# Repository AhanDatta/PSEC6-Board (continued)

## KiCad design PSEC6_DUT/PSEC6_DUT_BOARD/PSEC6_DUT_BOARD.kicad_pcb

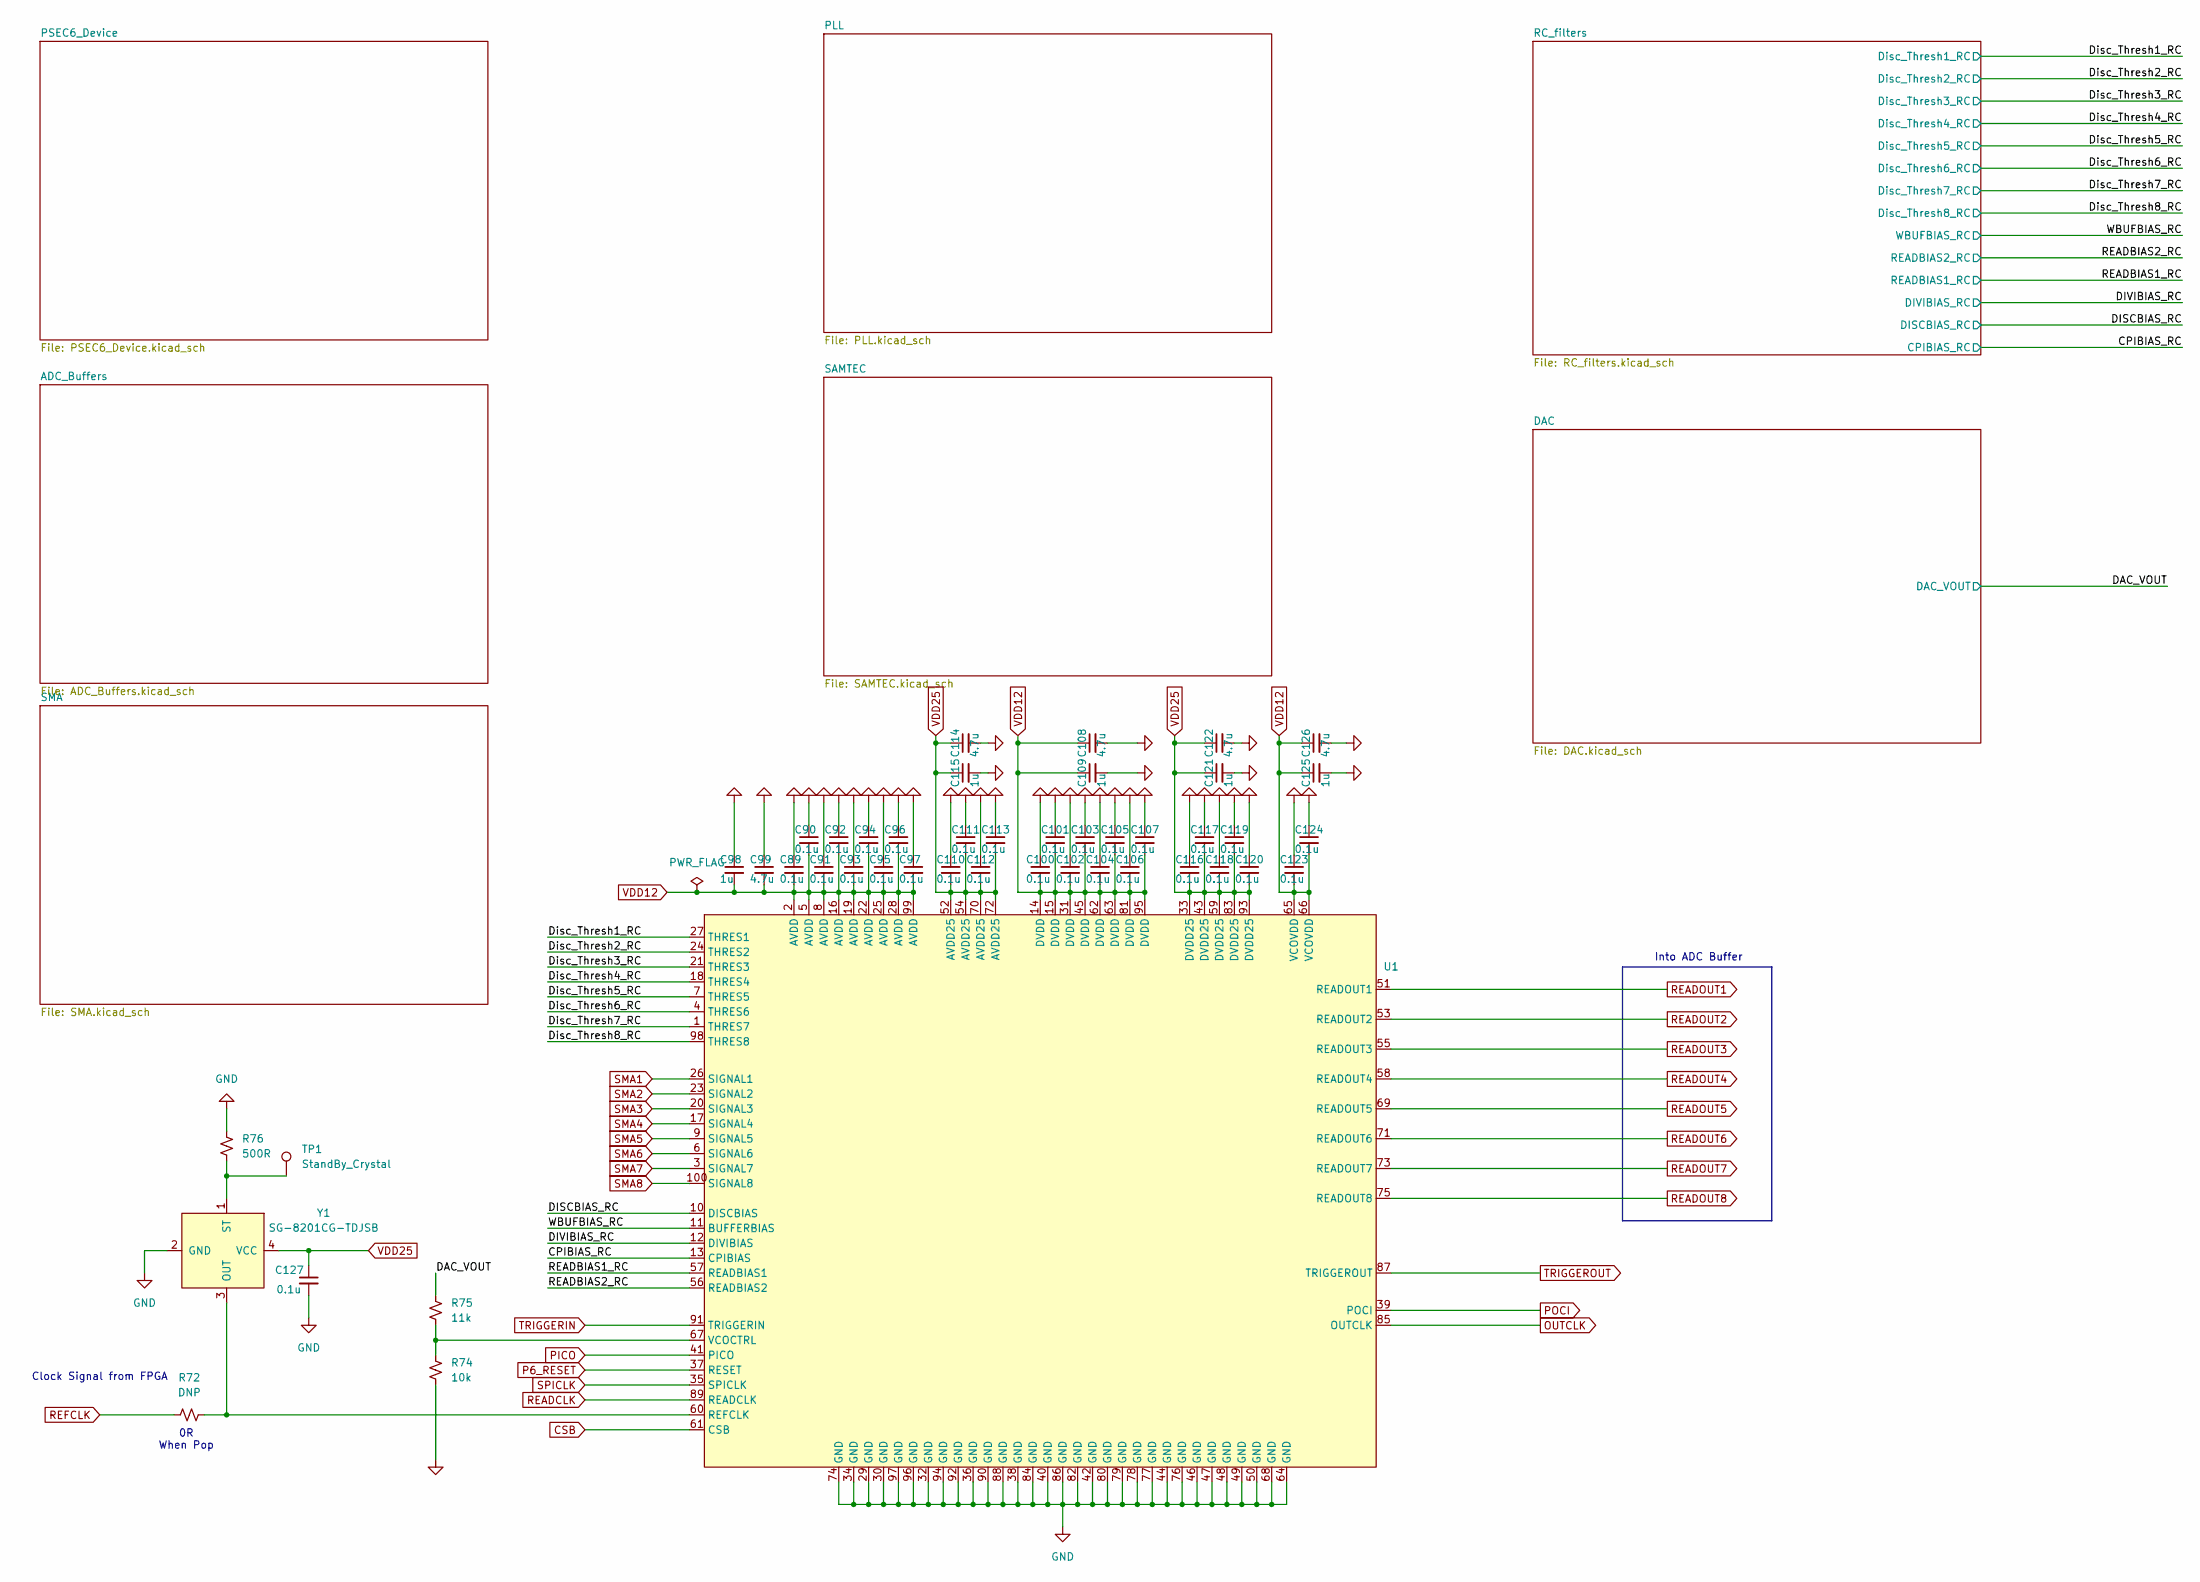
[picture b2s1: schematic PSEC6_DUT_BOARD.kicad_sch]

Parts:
C89, C90, C91, C92, C93, C94, C95, C96, C97, C100, C101, C102, C103, C104, C105, C106, C107, C110, C111, C112, C113, C116, C117, C118, C119, C120, C123, C124, C127: 0.1u; C_0603_1608Metric
C98, C109, C115, C121, C125: 1u; C_0603_1608Metric
C99, C108, C114, C122, C126: 4.7u; C_0603_1608Metric
R72: DNP; R_0603_1608Metric
R74: 10k; R_0603_1608Metric
R75: 11k; R_0603_1608Metric
R76: 500R; R_0603_1608Metric
TP1: StandBy_Crystal; TestPoint_THTPad_1.5x1.5mm_Drill0.7mm
U1: ArtInChip_QFN-100-1EP_12x12mm_P0.4mm_EP7.4x7.4mm
Y1: SG-8201CG-TDJSB

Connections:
/CPIBIAS_RC: U1.13 (CPIBIAS); also elsewhere on the board
/DAC_VOUT: R75.2; also elsewhere on the board
/DISCBIAS_RC: U1.10 (DISCBIAS); also elsewhere on the board
/DIVIBIAS_RC: U1.12 (DIVIBIAS); also elsewhere on the board
/Disc_Thresh1_RC: U1.27 (THRES1); also elsewhere on the board
/Disc_Thresh2_RC: U1.24 (THRES2); also elsewhere on the board
/Disc_Thresh3_RC: U1.21 (THRES3); also elsewhere on the board
/Disc_Thresh4_RC: U1.18 (THRES4); also elsewhere on the board
/Disc_Thresh5_RC: U1.7 (THRES5); also elsewhere on the board
/Disc_Thresh6_RC: U1.4 (THRES6); also elsewhere on the board
/Disc_Thresh7_RC: U1.1 (THRES7); also elsewhere on the board
/Disc_Thresh8_RC: U1.98 (THRES8); also elsewhere on the board
/READBIAS1_RC: U1.57 (READBIAS1); also elsewhere on the board
/READBIAS2_RC: U1.56 (READBIAS2); also elsewhere on the board
/WBUFBIAS_RC: U1.11 (BUFFERBIAS); also elsewhere on the board
CSB: U1.61 (CSB); also elsewhere on the board
GND: C89.1, C90.1, C91.1, C92.1, C93.1, C94.1, C95.1, C96.1, C97.1, C98.1, C99.1, C100.1, C101.1, C102.1, C103.1, C104.1, C105.1, C106.1, C107.1, C108.2, C109.2, C110.1, C111.1, C112.1, C113.1, C114.2, C115.2, C116.1, C117.1, C118.1, C119.1, C120.1, C121.2, C122.2, C123.1, C124.1, C125.2, C126.2, C127.2, R74.1, R76.2, U1.29 (GND), U1.30 (GND), U1.32 (GND), U1.34 (GND), U1.36 (GND), U1.38 (GND), U1.40 (GND), U1.42 (GND), U1.44 (GND), U1.46 (GND), U1.47 (GND), U1.48 (GND), U1.49 (GND), U1.50 (GND), U1.64 (GND), U1.68 (GND), U1.74 (GND), U1.76 (GND), U1.77 (GND), U1.78 (GND), U1.79 (GND), U1.80 (GND), U1.82 (GND), U1.84 (GND), U1.86 (GND), U1.88 (GND), U1.90 (GND), U1.92 (GND), U1.94 (GND), U1.96 (GND), U1.97 (GND), Y1.2 (GND); also elsewhere on the board
unnamed: R72.2, U1.60 (REFCLK), Y1.3 (OUT)
unnamed: R74.2, R75.1, U1.67 (VCOCTRL)
unnamed: R76.1, TP1.1 (1_1), Y1.1 (ST)
OUTCLK: U1.85 (OUTCLK); also elsewhere on the board
P6_RESET: U1.37 (RESET); also elsewhere on the board
PICO: U1.41 (PICO); also elsewhere on the board
POCI: U1.39 (POCI); also elsewhere on the board
READCLK: U1.89 (READCLK); also elsewhere on the board
READOUT1: U1.51 (READOUT1); also elsewhere on the board
READOUT2: U1.53 (READOUT2); also elsewhere on the board
READOUT3: U1.55 (READOUT3); also elsewhere on the board
READOUT4: U1.58 (READOUT4); also elsewhere on the board
READOUT5: U1.69 (READOUT5); also elsewhere on the board
READOUT6: U1.71 (READOUT6); also elsewhere on the board
READOUT7: U1.73 (READOUT7); also elsewhere on the board
READOUT8: U1.75 (READOUT8); also elsewhere on the board
REFCLK: R72.1; also elsewhere on the board
SMA1: U1.26 (SIGNAL1); also elsewhere on the board
SMA2: U1.23 (SIGNAL2); also elsewhere on the board
SMA3: U1.20 (SIGNAL3); also elsewhere on the board
SMA4: U1.17 (SIGNAL4); also elsewhere on the board
SMA5: U1.9 (SIGNAL5); also elsewhere on the board
SMA6: U1.6 (SIGNAL6); also elsewhere on the board
SMA7: U1.3 (SIGNAL7); also elsewhere on the board
SMA8: U1.100 (SIGNAL8); also elsewhere on the board
SPICLK: U1.35 (SPICLK); also elsewhere on the board
TRIGGERIN: U1.91 (TRIGGERIN); also elsewhere on the board
TRIGGEROUT: U1.87 (TRIGGEROUT); also elsewhere on the board
VDD12: C89.2, C90.2, C91.2, C92.2, C93.2, C94.2, C95.2, C96.2, C97.2, C98.2, C99.2, C100.2, C101.2, C102.2, C103.2, C104.2, C105.2, C106.2, C107.2, C108.1, C109.1, C123.2, C124.2, C125.1, C126.1, U1.2 (AVDD), U1.5 (AVDD), U1.8 (AVDD), U1.14 (DVDD), U1.15 (DVDD), U1.16 (AVDD), U1.19 (AVDD), U1.22 (AVDD), U1.25 (AVDD), U1.28 (AVDD), U1.31 (DVDD), U1.45 (DVDD), U1.62 (DVDD), U1.63 (DVDD), U1.65 (VCOVDD), U1.66 (VCOVDD), U1.81 (DVDD), U1.95 (DVDD), U1.99 (AVDD); also elsewhere on the board
VDD25: C110.2, C111.2, C112.2, C113.2, C114.1, C115.1, C116.2, C117.2, C118.2, C119.2, C120.2, C121.1, C122.1, C127.1, U1.33 (DVDD25), U1.43 (DVDD25), U1.52 (AVDD25), U1.54 (AVDD25), U1.59 (DVDD25), U1.70 (AVDD25), U1.72 (AVDD25), U1.83 (DVDD25), U1.93 (DVDD25), Y1.4 (VCC); also elsewhere on the board

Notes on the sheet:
0R When Pop
Into ADC Buffer
Clock Signal from FPGA

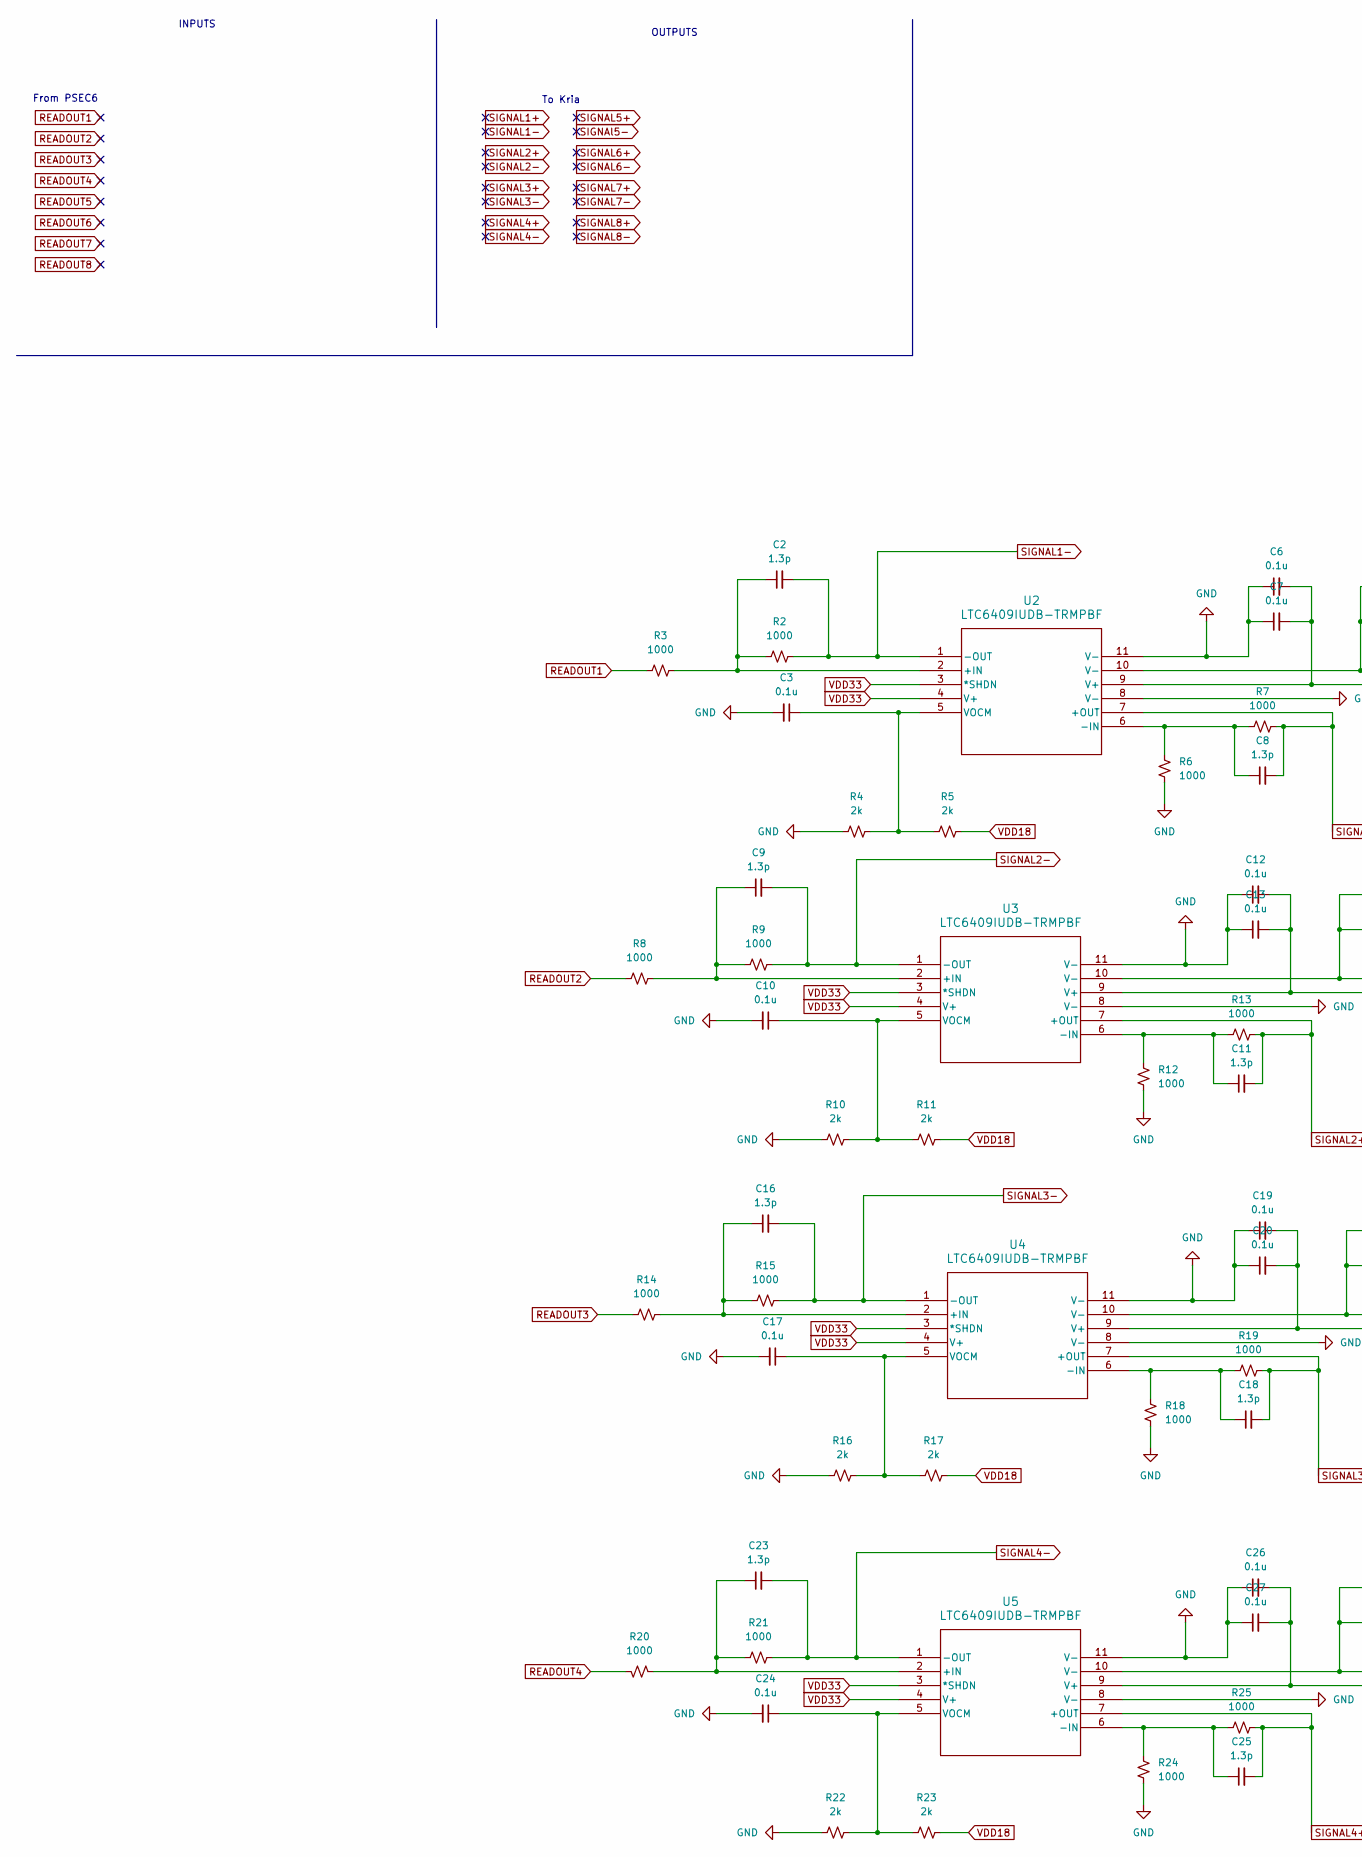
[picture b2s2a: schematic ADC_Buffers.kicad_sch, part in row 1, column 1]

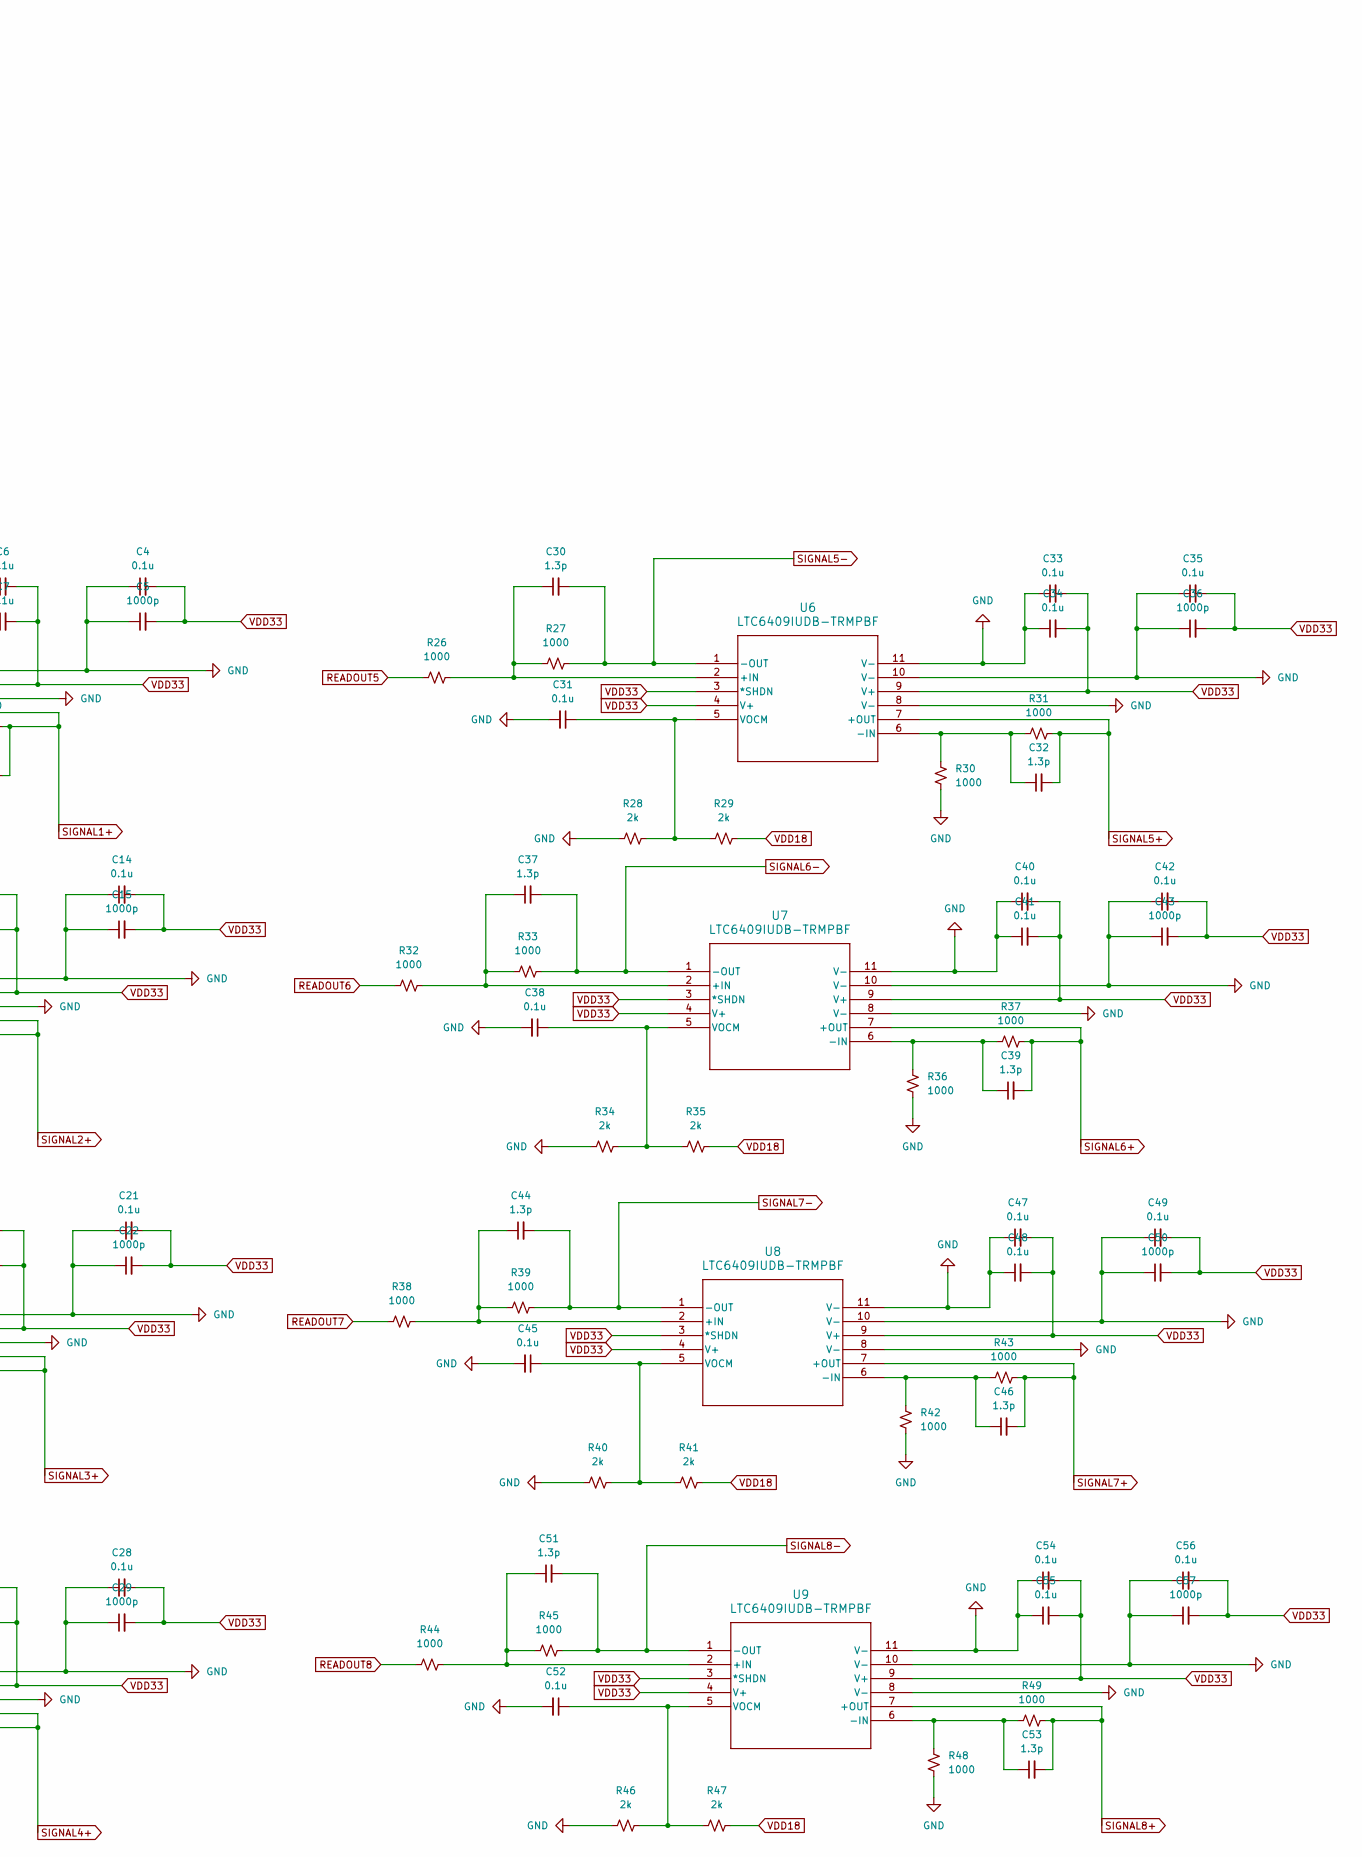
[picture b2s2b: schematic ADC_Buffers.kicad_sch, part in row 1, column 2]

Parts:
C2, C8, C9, C11, C16, C18, C23, C25, C30, C32, C37, C39, C44, C46, C51, C53: 1.3p; C_0603_1608Metric
C3, C4, C6, C7, C10, C12, C13, C14, C17, C19, C20, C21, C24, C26, C27, C28, C31, C33, C34, C35, C38, C40, C41, C42, C45, C47, C48, C49, C52, C54, C55, C56: 0.1u; C_0603_1608Metric
C5, C15, C22, C29, C36, C43, C50, C57: 1000p; C_0603_1608Metric
R2, R3, R6, R7, R8, R9, R12, R13, R14, R15, R18, R19, R20, R21, R24, R25, R26, R27, R30, R31, R32, R33, R36, R37, R38, R39, R42, R43, R44, R45, R48, R49: 1000; R_0603_1608Metric
R4, R5, R10, R11, R16, R17, R22, R23, R28, R29, R34, R35, R40, R41, R46, R47: 2k; R_0603_1608Metric
U2, U3, U4, U5, U6, U7, U8, U9: LTC6409IUDB-TRMPBF; QFN-10_UDB_LIT

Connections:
GND: C3.2, C4.1, C5.1, C6.1, C7.1, C10.2, C12.1, C13.1, C14.1, C15.1, C17.2, C19.1, C20.1, C21.1, C22.1, C24.2, C26.1, C27.1, C28.1, C29.1, C31.2, C33.1, C34.1, C35.1, C36.1, C38.2, C40.1, C41.1, C42.1, C43.1, C45.2, C47.1, C48.1, C49.1, C50.1, C52.2, C54.1, C55.1, C56.1, C57.1, R4.1, R6.1, R10.1, R12.1, R16.1, R18.1, R22.1, R24.1, R28.1, R30.1, R34.1, R36.1, R40.1, R42.1, R46.1, R48.1, U2.8 (V-), U2.10 (V-), U2.11 (V-), U3.8 (V-), U3.10 (V-), U3.11 (V-), U4.8 (V-), U4.10 (V-), U4.11 (V-), U5.8 (V-), U5.10 (V-), U5.11 (V-), U6.8 (V-), U6.10 (V-), U6.11 (V-), U7.8 (V-), U7.10 (V-), U7.11 (V-), U8.8 (V-), U8.10 (V-), U8.11 (V-), U9.8 (V-), U9.10 (V-), U9.11 (V-); also elsewhere on the board
unnamed: C2.1, R2.1, R3.2, U2.2 (+IN)
unnamed: C8.1, R6.2, R7.2, U2.6 (-IN)
unnamed: C3.1, R4.2, R5.1, U2.5 (VOCM)
unnamed: C9.1, R8.2, R9.1, U3.2 (+IN)
unnamed: C11.1, R12.2, R13.2, U3.6 (-IN)
unnamed: C10.1, R10.2, R11.1, U3.5 (VOCM)
unnamed: C16.1, R14.2, R15.1, U4.2 (+IN)
unnamed: C18.1, R18.2, R19.2, U4.6 (-IN)
unnamed: C17.1, R16.2, R17.1, U4.5 (VOCM)
unnamed: C23.1, R20.1, R21.1, U5.2 (+IN)
unnamed: C25.1, R24.2, R25.2, U5.6 (-IN)
unnamed: C24.1, R22.2, R23.1, U5.5 (VOCM)
unnamed: C30.1, R26.2, R27.1, U6.2 (+IN)
unnamed: C32.1, R30.2, R31.2, U6.6 (-IN)
unnamed: C31.1, R28.2, R29.1, U6.5 (VOCM)
unnamed: C37.1, R32.2, R33.1, U7.2 (+IN)
unnamed: C39.1, R36.2, R37.2, U7.6 (-IN)
unnamed: C38.1, R34.2, R35.1, U7.5 (VOCM)
unnamed: C44.1, R38.2, R39.1, U8.2 (+IN)
unnamed: C46.1, R42.2, R43.2, U8.6 (-IN)
unnamed: C45.1, R40.2, R41.1, U8.5 (VOCM)
unnamed: C51.1, R44.2, R45.1, U9.2 (+IN)
unnamed: C53.1, R48.2, R49.2, U9.6 (-IN)
unnamed: C52.1, R46.2, R47.1, U9.5 (VOCM)
READOUT1: R3.1; also elsewhere on the board
READOUT2: R8.1; also elsewhere on the board
READOUT3: R14.1; also elsewhere on the board
READOUT4: R20.2; also elsewhere on the board
READOUT5: R26.1; also elsewhere on the board
READOUT6: R32.1; also elsewhere on the board
READOUT7: R38.1; also elsewhere on the board
READOUT8: R44.1; also elsewhere on the board
SIGNAL1+: C8.2, R7.1, U2.7 (+OUT); also elsewhere on the board
SIGNAL1-: C2.2, R2.2, U2.1 (-OUT); also elsewhere on the board
SIGNAL2+: C11.2, R13.1, U3.7 (+OUT); also elsewhere on the board
SIGNAL2-: C9.2, R9.2, U3.1 (-OUT); also elsewhere on the board
SIGNAL3+: C18.2, R19.1, U4.7 (+OUT); also elsewhere on the board
SIGNAL3-: C16.2, R15.2, U4.1 (-OUT); also elsewhere on the board
SIGNAL4+: C25.2, R25.1, U5.7 (+OUT); also elsewhere on the board
SIGNAL4-: C23.2, R21.2, U5.1 (-OUT); also elsewhere on the board
SIGNAL5+: C32.2, R31.1, U6.7 (+OUT); also elsewhere on the board
SIGNAL5-: C30.2, R27.2, U6.1 (-OUT); also elsewhere on the board
SIGNAL6+: C39.2, R37.1, U7.7 (+OUT); also elsewhere on the board
SIGNAL6-: C37.2, R33.2, U7.1 (-OUT); also elsewhere on the board
SIGNAL7+: C46.2, R43.1, U8.7 (+OUT); also elsewhere on the board
SIGNAL7-: C44.2, R39.2, U8.1 (-OUT); also elsewhere on the board
SIGNAL8+: C53.2, R49.1, U9.7 (+OUT); also elsewhere on the board
SIGNAL8-: C51.2, R45.2, U9.1 (-OUT); also elsewhere on the board
VDD18: R5.2, R11.2, R17.2, R23.2, R29.2, R35.2, R41.2, R47.2; also elsewhere on the board
VDD33: C4.2, C5.2, C6.2, C7.2, C12.2, C13.2, C14.2, C15.2, C19.2, C20.2, C21.2, C22.2, C26.2, C27.2, C28.2, C29.2, C33.2, C34.2, C35.2, C36.2, C40.2, C41.2, C42.2, C43.2, C47.2, C48.2, C49.2, C50.2, C54.2, C55.2, C56.2, C57.2, U2.3 (*SHDN), U2.4 (V+), U2.9 (V+), U3.3 (*SHDN), U3.4 (V+), U3.9 (V+), U4.3 (*SHDN), U4.4 (V+), U4.9 (V+), U5.3 (*SHDN), U5.4 (V+), U5.9 (V+), U6.3 (*SHDN), U6.4 (V+), U6.9 (V+), U7.3 (*SHDN), U7.4 (V+), U7.9 (V+), U8.3 (*SHDN), U8.4 (V+), U8.9 (V+), U9.3 (*SHDN), U9.4 (V+), U9.9 (V+); also elsewhere on the board

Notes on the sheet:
OUTPUTS
From PSEC6
INPUTS
To Kria

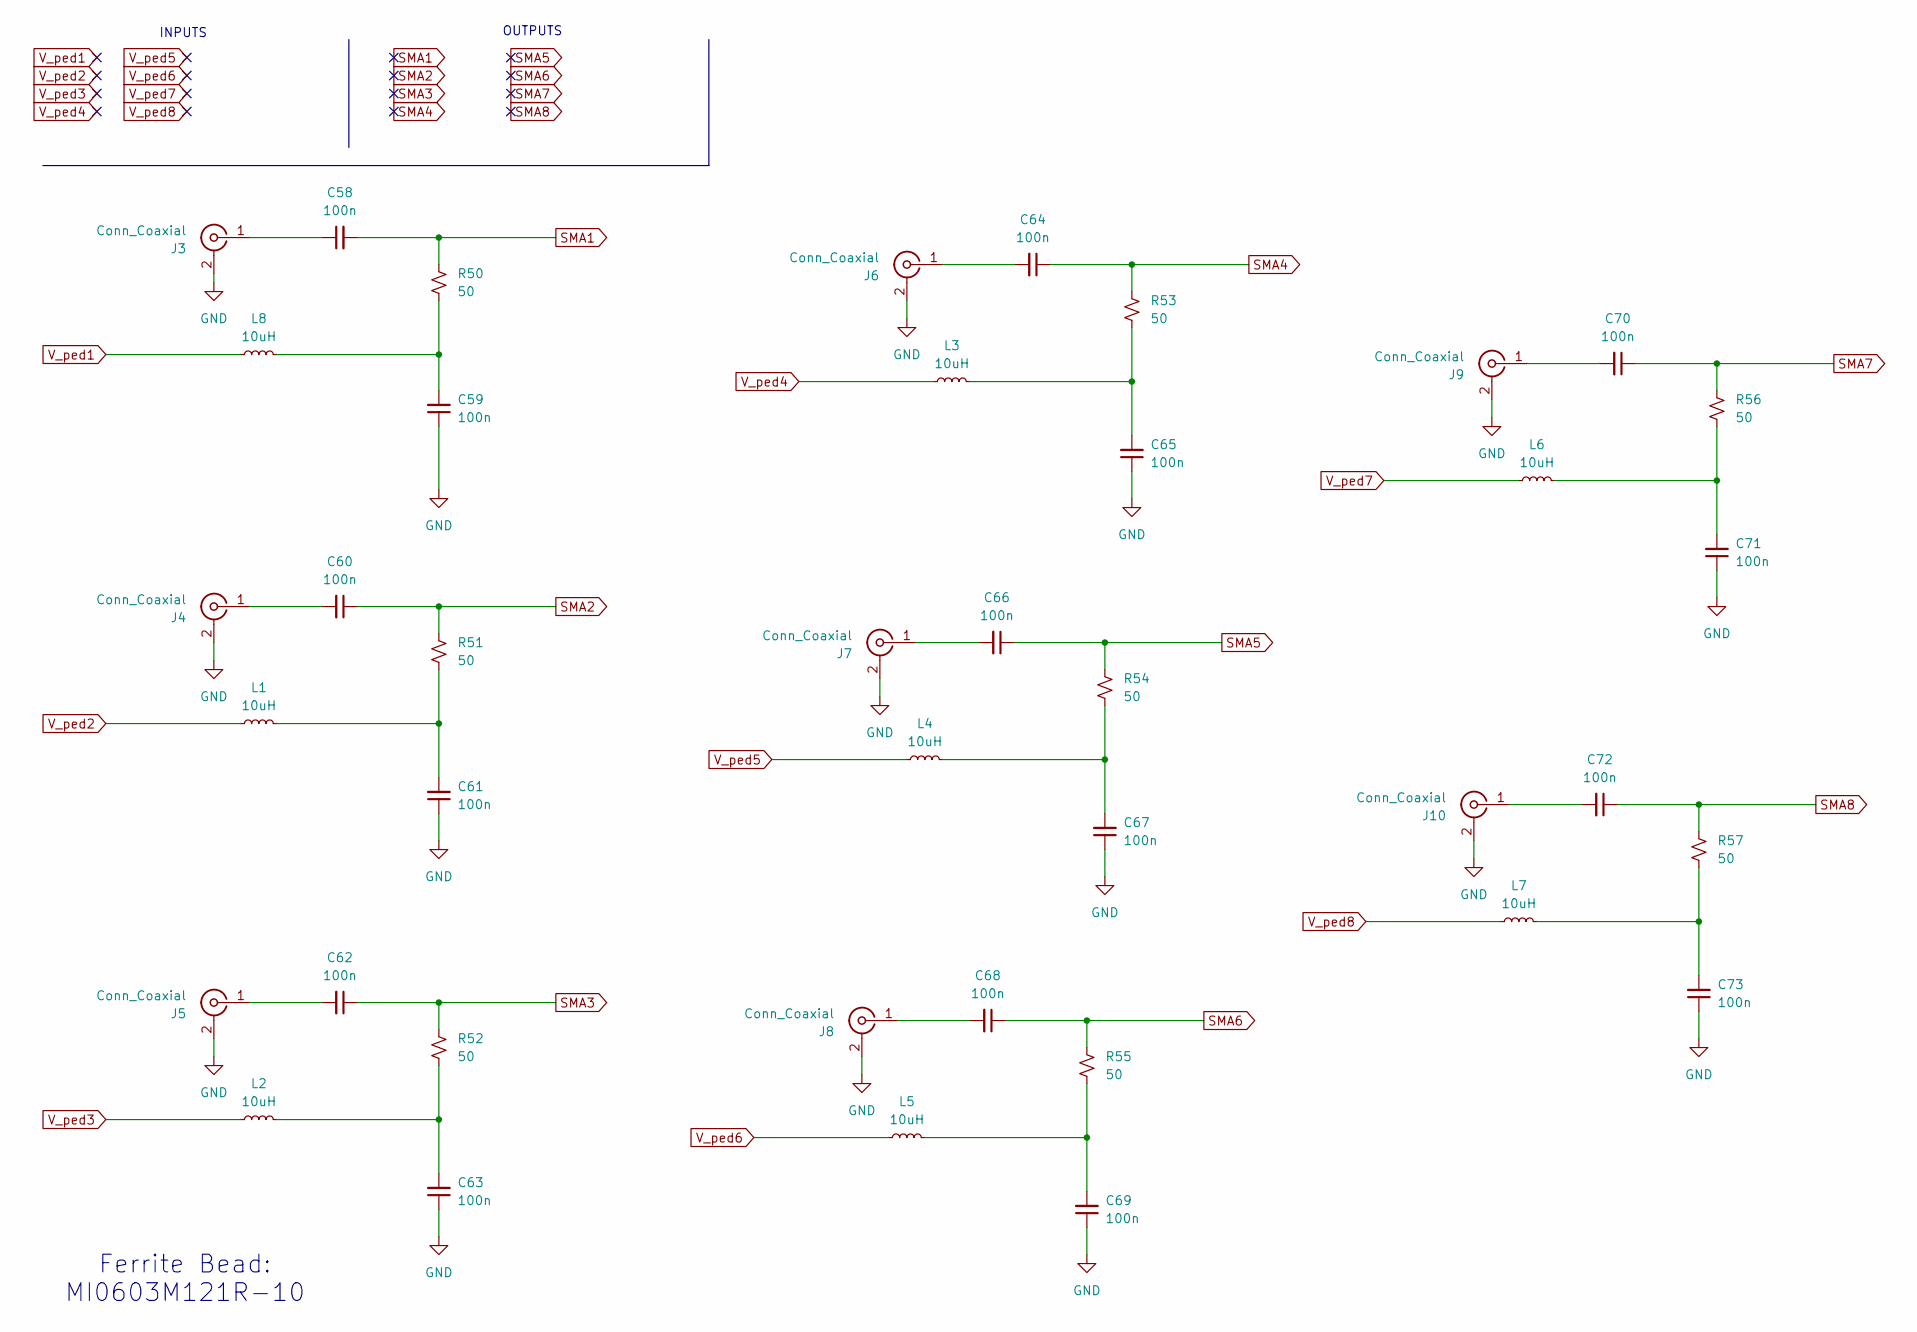
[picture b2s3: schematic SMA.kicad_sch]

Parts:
C58, C59, C60, C61, C62, C63, C64, C65, C66, C67, C68, C69, C70, C71, C72, C73: 100n; C_0603_1608Metric
J3, J4, J5, J6, J7, J8, J9, J10: Conn_Coaxial; SMA_Amphenol_132134-14_Vertical
L1, L2, L3, L4, L5, L6, L7, L8: 10uH; IND_LQH2MCN100K02L
R50, R51, R52, R53, R54, R55, R56, R57: 50; R_0603_1608Metric

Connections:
GND: C59.1, C61.1, C63.1, C65.1, C67.1, C69.1, C71.1, C73.1, J3.2 (Ext), J4.2 (Ext), J5.2 (Ext), J6.2 (Ext), J7.2 (Ext), J8.2 (Ext), J9.2 (Ext), J10.2 (Ext); also elsewhere on the board
unnamed: C59.2, L8.2, R50.2
unnamed: C61.2, L1.2, R51.2
unnamed: C63.2, L2.2, R52.2
unnamed: C65.2, L3.2, R53.2
unnamed: C67.2, L4.2, R54.2
unnamed: C69.2, L5.2, R55.2
unnamed: C71.2, L6.2, R56.2
unnamed: C73.2, L7.2, R57.2
unnamed: C58.1, J3.1 (In)
unnamed: C60.2, J4.1 (In)
unnamed: C62.2, J5.1 (In)
unnamed: C64.2, J6.1 (In)
unnamed: C66.2, J7.1 (In)
unnamed: C68.2, J8.1 (In)
unnamed: C70.2, J9.1 (In)
unnamed: C72.2, J10.1 (In)
SMA1: C58.2, R50.1; also elsewhere on the board
SMA2: C60.1, R51.1; also elsewhere on the board
SMA3: C62.1, R52.1; also elsewhere on the board
SMA4: C64.1, R53.1; also elsewhere on the board
SMA5: C66.1, R54.1; also elsewhere on the board
SMA6: C68.1, R55.1; also elsewhere on the board
SMA7: C70.1, R56.1; also elsewhere on the board
SMA8: C72.1, R57.1; also elsewhere on the board
V_ped1: L8.1; also elsewhere on the board
V_ped2: L1.1; also elsewhere on the board
V_ped3: L2.1; also elsewhere on the board
V_ped4: L3.1; also elsewhere on the board
V_ped5: L4.1; also elsewhere on the board
V_ped6: L5.1; also elsewhere on the board
V_ped7: L6.1; also elsewhere on the board
V_ped8: L7.1; also elsewhere on the board

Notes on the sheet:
OUTPUTS
Ferrite Bead: MI0603M121R-10
INPUTS

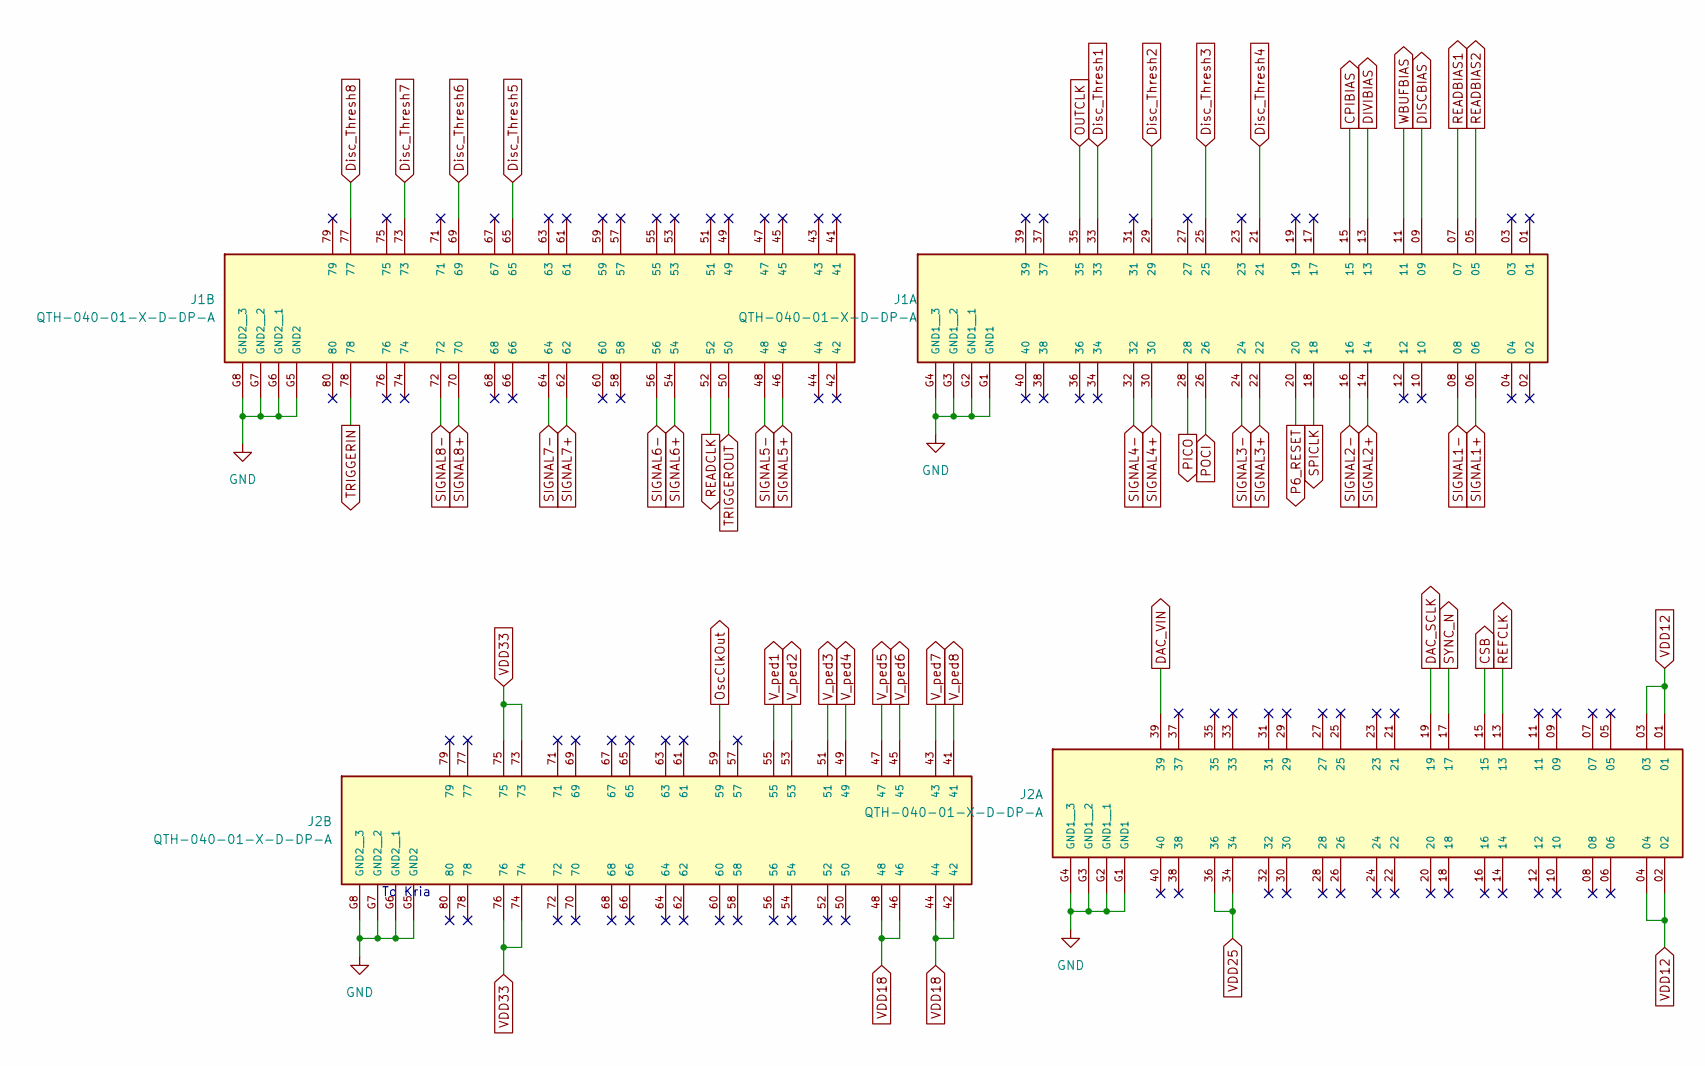
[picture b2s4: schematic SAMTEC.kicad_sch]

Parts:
J1, J2: QTH-040-01-X-D-DP-A; SAMTEC_QTH-040-01-X-D-DP-A; PARTREV L

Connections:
CPIBIAS: J1.15; also elsewhere on the board
CSB: J2.15; also elsewhere on the board
DAC_SCLK: J2.19; also elsewhere on the board
DAC_VIN: J2.39; also elsewhere on the board
DISCBIAS: J1.09; also elsewhere on the board
DIVIBIAS: J1.13; also elsewhere on the board
Disc_Thresh1: J1.33; also elsewhere on the board
Disc_Thresh2: J1.29; also elsewhere on the board
Disc_Thresh3: J1.25; also elsewhere on the board
Disc_Thresh4: J1.21; also elsewhere on the board
Disc_Thresh5: J1.77; also elsewhere on the board
Disc_Thresh6: J1.73; also elsewhere on the board
Disc_Thresh7: J1.69; also elsewhere on the board
Disc_Thresh8: J1.65; also elsewhere on the board
GND: J1.G1 (GND1), J1.G2 (GND1__1), J1.G3 (GND1__2), J1.G4 (GND1__3), J1.G5 (GND2), J1.G6 (GND2__1), J1.G7 (GND2__2), J1.G8 (GND2__3), J2.G1 (GND1), J2.G2 (GND1__1), J2.G3 (GND1__2), J2.G4 (GND1__3), J2.G5 (GND2), J2.G6 (GND2__1), J2.G7 (GND2__2), J2.G8 (GND2__3); also elsewhere on the board
OUTCLK: J1.35; also elsewhere on the board
OscClkOut: J2.59
P6_RESET: J1.20; also elsewhere on the board
PICO: J1.28; also elsewhere on the board
POCI: J1.26; also elsewhere on the board
READBIAS1: J1.07; also elsewhere on the board
READBIAS2: J1.05; also elsewhere on the board
READCLK: J1.52; also elsewhere on the board
REFCLK: J2.13; also elsewhere on the board
SIGNAL1+: J1.06; also elsewhere on the board
SIGNAL1-: J1.08; also elsewhere on the board
SIGNAL2+: J1.14; also elsewhere on the board
SIGNAL2-: J1.16; also elsewhere on the board
SIGNAL3+: J1.22; also elsewhere on the board
SIGNAL3-: J1.24; also elsewhere on the board
SIGNAL4+: J1.30; also elsewhere on the board
SIGNAL4-: J1.32; also elsewhere on the board
SIGNAL5+: J1.46; also elsewhere on the board
SIGNAL5-: J1.48; also elsewhere on the board
SIGNAL6+: J1.54; also elsewhere on the board
SIGNAL6-: J1.56; also elsewhere on the board
SIGNAL7+: J1.62; also elsewhere on the board
SIGNAL7-: J1.64; also elsewhere on the board
SIGNAL8+: J1.70; also elsewhere on the board
SIGNAL8-: J1.72; also elsewhere on the board
SPICLK: J1.18; also elsewhere on the board
SYNC_N: J2.17; also elsewhere on the board
TRIGGERIN: J1.78; also elsewhere on the board
TRIGGEROUT: J1.50; also elsewhere on the board
VDD12: J2.01, J2.02, J2.03, J2.04; also elsewhere on the board
VDD18: J2.42, J2.44, J2.46, J2.48; also elsewhere on the board
VDD25: J2.34, J2.36; also elsewhere on the board
VDD33: J2.73, J2.74, J2.75, J2.76; also elsewhere on the board
V_ped1: J2.55; also elsewhere on the board
V_ped2: J2.53; also elsewhere on the board
V_ped3: J2.51; also elsewhere on the board
V_ped4: J2.49; also elsewhere on the board
V_ped5: J2.47; also elsewhere on the board
V_ped6: J2.45; also elsewhere on the board
V_ped7: J2.43; also elsewhere on the board
V_ped8: J2.41; also elsewhere on the board
WBUFBIAS: J1.11; also elsewhere on the board

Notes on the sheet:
To Kria
